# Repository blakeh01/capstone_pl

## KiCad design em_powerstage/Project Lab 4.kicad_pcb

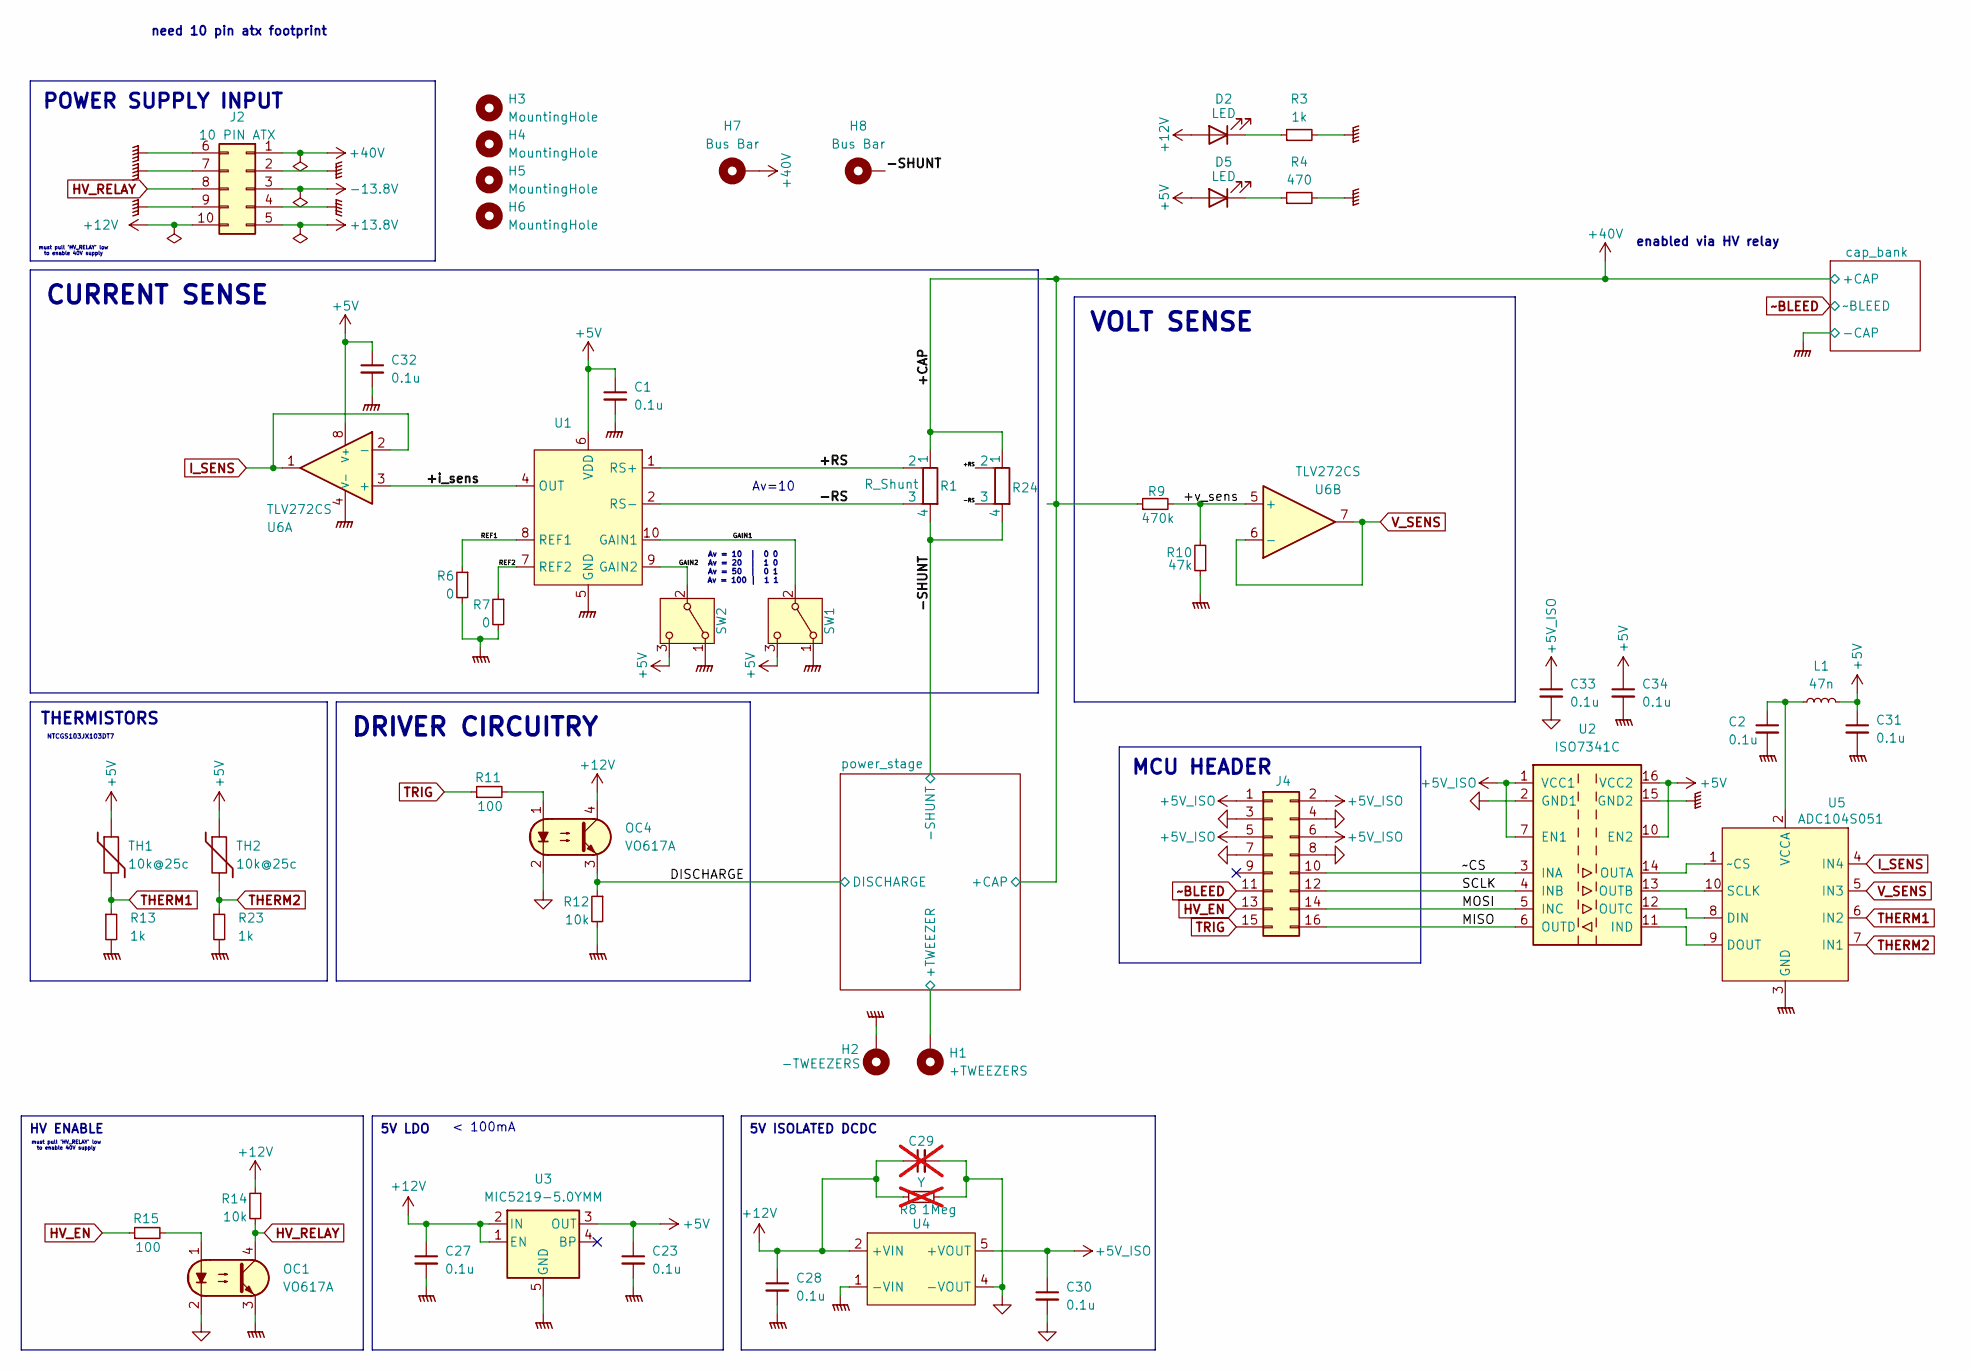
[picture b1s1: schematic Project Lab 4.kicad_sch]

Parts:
C1, C2, C23, C27, C28, C30, C31, C32, C33, C34: 0.1u; C_1206_3216Metric_Pad1.33x1.80mm_HandSolder
C29: Y; C_Disc_D8.0mm_W2.5mm_P5.00mm; not fitted
D2, D5: LED; LED_1206_3216Metric_Pad1.42x1.75mm_HandSolder
H1: +TWEEZERS; MountingHole_4.3mm_M4_Pad
H2: -TWEEZERS; MountingHole_4.3mm_M4_Pad
H3, H4, H5, H6: MountingHole; MountingHole_4mm
H7: Bus Bar; busbar_28mmX155mm
H8: Bus Bar; busbar_35mm_18mm
J2: 10 PIN ATX; Molex_Mini-Fit_Jr_5566-10A_2x05_P4.20mm_Vertical
J4: Conn_02x08_Odd_Even; PinHeader_2x08_P2.54mm_Vertical
L1: 47n; L_1206_3216Metric_Pad1.22x1.90mm_HandSolder
OC1, OC4: VO617A; DIP-4_W7.62mm_LongPads
R1: R_Shunt; CSS4J4026RL500F
R3, R13, R23: 1k; R_0805_2012Metric_Pad1.20x1.40mm_HandSolder
R4: 470; R_0805_2012Metric_Pad1.20x1.40mm_HandSolder
R6, R7: 0; R_0805_2012Metric_Pad1.20x1.40mm_HandSolder
R8: 1Meg; R_Axial_DIN0207_L6.3mm_D2.5mm_P15.24mm_Horizontal; not fitted
R9: 470k; R_0805_2012Metric_Pad1.20x1.40mm_HandSolder
R10: 47k; R_0805_2012Metric_Pad1.20x1.40mm_HandSolder
R11, R15: 100; R_0805_2012Metric_Pad1.20x1.40mm_HandSolder
R12, R14: 10k; R_0805_2012Metric_Pad1.20x1.40mm_HandSolder
R24: R_Shunt; CSM2F6918L050J21
SW1, SW2: SW_SPDT; SW_E-Switch_EG1271_SPDT
TH1, TH2: 10k@25c; R_0402_1005Metric_Pad0.72x0.64mm_HandSolder
U1: TDFN-10-SMD
U2: ISO7341C; SOIC-16W_7.5x10.3mm_P1.27mm
U3: MIC5219-5.0YMM; MSOP-8_3x3mm_P0.65mm
U4: 1769405241
U5: ADC104S051; MSOP-10-1EP_3x3mm_P0.5mm_EP1.73x1.98mm
U6: TLV272CS; SO-8_3.9x4.9mm_P1.27mm

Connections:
+5V: C1.1, C23.1, C31.1, C32.1, C34.1, D5.2 (A), L1.2, SW1.3 (C), SW2.3 (C), TH1.1, TH2.1, U1.6 (VDD), U2.10 (EN2), U2.16 (VCC2), U3.3 (OUT), U6.8 (V+)
+5V_ISO: C30.1, C33.1, J4.1, J4.2, J4.5, J4.6, U2.1 (VCC1), U2.7 (EN1), U4.5 (+VOUT)
+12V: C27.1, C28.1, C29.1, D2.2 (A), J2.10, OC4.4, R8.1, R14.1, U3.1 (EN), U3.2 (IN), U4.2 (+VIN); also elsewhere on the board
+13.8V: J2.5
+40V: H7.1, J2.1, R1.1, R9.1, R24.1; also elsewhere on the board
-13.8V: J2.3
/+RS: R1.2, R24.2, U1.1 (RS+)
/+i_sens: U1.4 (OUT), U6.3 (+)
/+v_sens: R9.2, R10.2, U6.5 (+)
/-RS: R1.3, R24.3, U1.2 (RS-)
/-SHUNT: H8.1, R1.4, R24.4; also elsewhere on the board
/DISCHARGE: OC4.3, R12.1; also elsewhere on the board
/GAIN1: SW1.2 (B), U1.10 (GAIN1)
/GAIN2: SW2.2 (B), U1.9 (GAIN2)
/MISO: J4.16, U2.6 (OUTD)
/MOSI: J4.14, U2.5 (INC)
/REF1: R6.1, U1.8 (REF1)
/REF2: R7.1, U1.7 (REF2)
/SCLK: J4.12, U2.4 (INB)
/power_stage/+TWEEZER: H1.1; also elsewhere on the board
/~CS: J4.10, U2.3 (INA)
GND: C29.2, C30.2, C33.2, J4.3, J4.4, J4.7, J4.8, OC1.2, OC4.2, R8.2, U2.2 (GND1), U2.8 (GND1), U4.4 (-VOUT); also elsewhere on the board
GNDPWR: C1.2, C2.2, C23.2, C27.2, C28.2, C31.2, C32.2, C34.2, H2.1, J2.2, J2.4, J2.6, J2.7, J2.9, OC1.3, R3.2, R4.2, R6.2, R7.2, R10.1, R12.2, R13.2, R23.2, SW1.1 (A), SW2.1 (A), U1.5 (GND), U2.9 (GND2), U2.15 (GND2), U3.5 (GND), U3.6 (GND), U3.7 (GND), U3.8 (GND), U4.1 (-VIN), U5.3 (GND), U6.4 (V-); also elsewhere on the board
HV_EN: J4.13, R15.1
HV_RELAY: J2.8, OC1.4, R14.2
I_SENS: U5.4 (IN4), U6.1, U6.2 (-)
unnamed: D2.1 (K), R3.1
unnamed: D5.1 (K), R4.1
unnamed: OC1.1, R15.2
unnamed: OC4.1, R11.2
unnamed: U2.11 (IND), U5.9 (DOUT)
unnamed: U2.14 (OUTA), U5.1 (~CS)
unnamed: U2.13 (OUTB), U5.10 (SCLK)
unnamed: U2.12 (OUTC), U5.8 (DIN)
unnamed: C2.1, L1.1, U5.2 (VCCA)
THERM1: R13.1, TH1.2, U5.6 (IN2)
THERM2: R23.1, TH2.2, U5.7 (IN1)
TRIG: J4.15, R11.1
V_SENS: U5.5 (IN3), U6.6 (-), U6.7
~BLEED: J4.11; also elsewhere on the board

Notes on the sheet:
POWER SUPPLY INPUT
5V ISOLATED DCDC
MCU HEADER
HV ENABLE
DRIVER CIRCUITRY
5V LDO
CURRENT SENSE
VOLT SENSE
THERMISTORS
must pull 'HV_RELAY' low to enable 40V supply
enabled via HV relay
NTCGS103JX103DT7
need 10 pin atx footprint
< 100mA
Av = 10 | 0 0 Av = 20 | 1 0 Av = 50 | 0 1 Av = 100 | 1 1
Av=10

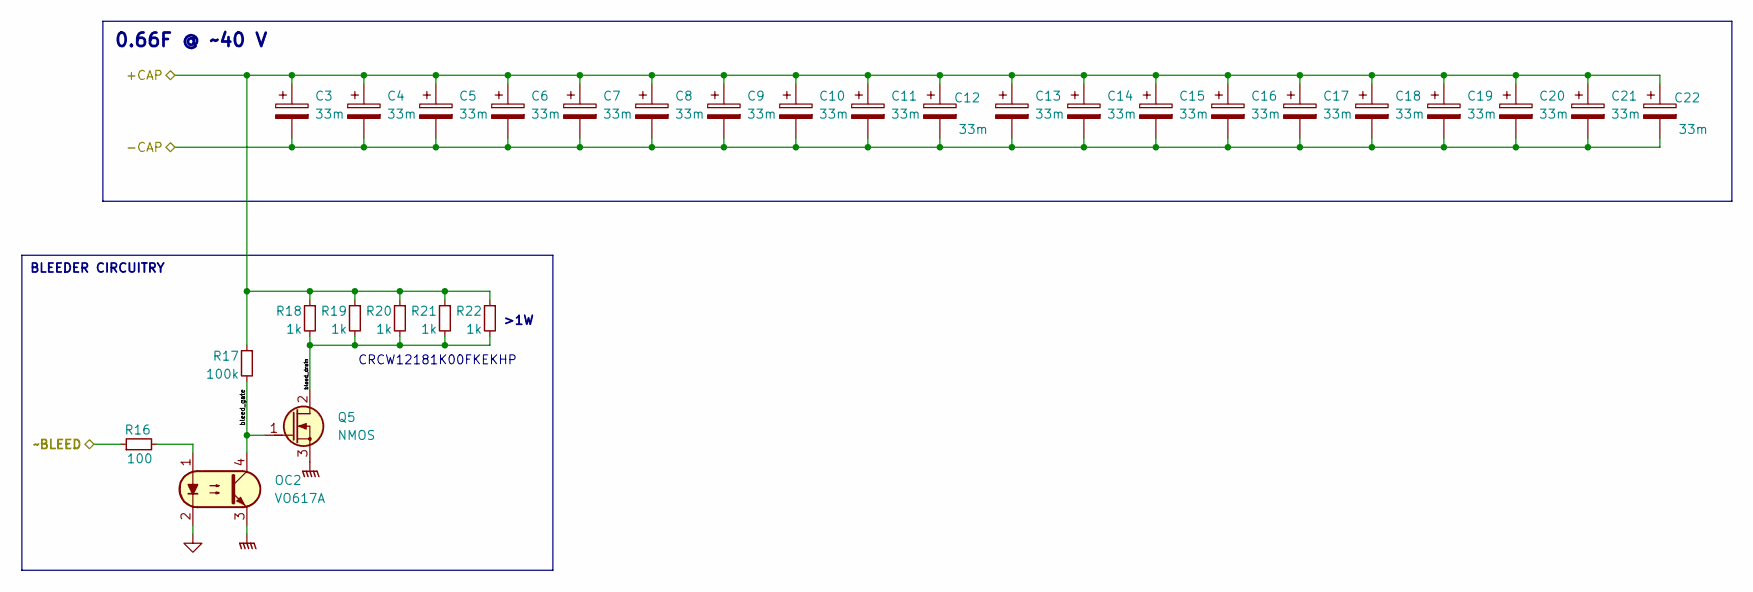
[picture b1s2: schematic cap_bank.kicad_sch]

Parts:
C3, C4, C5, C6, C7, C8, C9, C10, C11, C12, C13, C14, C15, C16, C17, C18, C19, C20, C21, C22: 33m; CAPPRD1000W190D3550H8200
OC2: VO617A; DIP-4_W7.62mm_LongPads
Q5: NMOS; SOT-23-3
R16: 100; R_0805_2012Metric_Pad1.20x1.40mm_HandSolder
R17: 100k; R_0805_2012Metric_Pad1.20x1.40mm_HandSolder
R18, R19, R20, R21, R22: 1k; R_1218_3246Metric_Pad1.22x4.75mm_HandSolder

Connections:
+40V: C3.1, C4.1, C5.1, C6.1, C7.1, C8.1, C9.1, C10.1, C11.1, C12.1, C13.1, C14.1, C15.1, C16.1, C17.1, C18.1, C19.1, C20.1, C21.1, C22.1, R17.1, R18.1, R19.1, R20.1, R21.1, R22.1; also elsewhere on the board
/cap_bank/bleed_drain: Q5.2 (D), R18.2, R19.2, R20.2, R21.2, R22.2
/cap_bank/bleed_gate: OC2.4, Q5.1 (G), R17.2
GND: OC2.2; also elsewhere on the board
GNDPWR: C3.2, C4.2, C5.2, C6.2, C7.2, C8.2, C9.2, C10.2, C11.2, C12.2, C13.2, C14.2, C15.2, C16.2, C17.2, C18.2, C19.2, C20.2, C21.2, C22.2, OC2.3, Q5.3 (S); also elsewhere on the board
unnamed: OC2.1, R16.2
~BLEED: R16.1; also elsewhere on the board

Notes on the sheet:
BLEEDER CIRCUITRY
0.66F @ ~40 V
CRCW12181K00FKEKHP
>1W

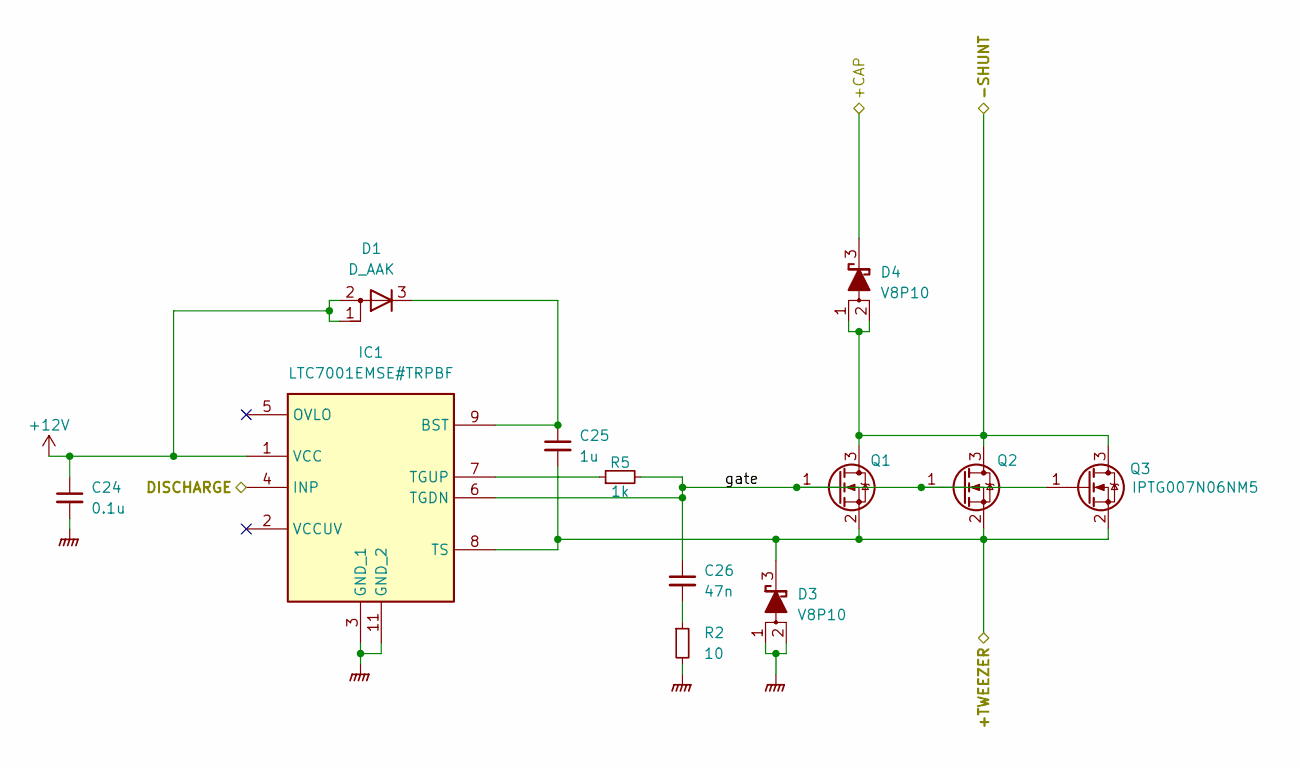
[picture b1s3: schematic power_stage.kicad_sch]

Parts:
C24: 0.1u; C_1206_3216Metric_Pad1.33x1.80mm_HandSolder
C25: 1u; C_1206_3216Metric_Pad1.33x1.80mm_HandSolder
C26: 47n; C_0805_2012Metric_Pad1.18x1.45mm_HandSolder
D1: D_AAK; SOT-23-3
D3, D4: V8P10; TO-277A
IC1: LTC7001EMSE#TRPBF; SOP50P490X110-11N; Mouser Part Number 584-7001EMSETRPBF
Q1, Q2, Q3: IPTG007N06NM5; HSOG_8-3
R2: 10; R_0805_2012Metric_Pad1.20x1.40mm_HandSolder
R5: 1k; R_0805_2012Metric_Pad1.20x1.40mm_HandSolder

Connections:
+12V: C24.1, D1.1 (A), D1.2 (A), IC1.1 (VCC); also elsewhere on the board
+40V: D4.3 (K); also elsewhere on the board
/-SHUNT: D4.1 (A), D4.2 (A), Q1.3 (D), Q2.3 (D), Q3.3 (D); also elsewhere on the board
/DISCHARGE: IC1.4 (INP); also elsewhere on the board
/power_stage/+TWEEZER: C25.2, D3.3 (K), IC1.8 (TS), Q1.2 (S), Q2.2 (S), Q3.2 (S); also elsewhere on the board
/power_stage/gate: C26.1, IC1.6 (TGDN), Q1.1 (G), Q2.1 (G), Q3.1 (G), R5.2
GNDPWR: C24.2, D3.1 (A), D3.2 (A), IC1.3 (GND_1), IC1.11 (GND_2), R2.2; also elsewhere on the board
unnamed: C26.2, R2.1
unnamed: C25.1, D1.3 (K), IC1.9 (BST)
unnamed: IC1.7 (TGUP), R5.1

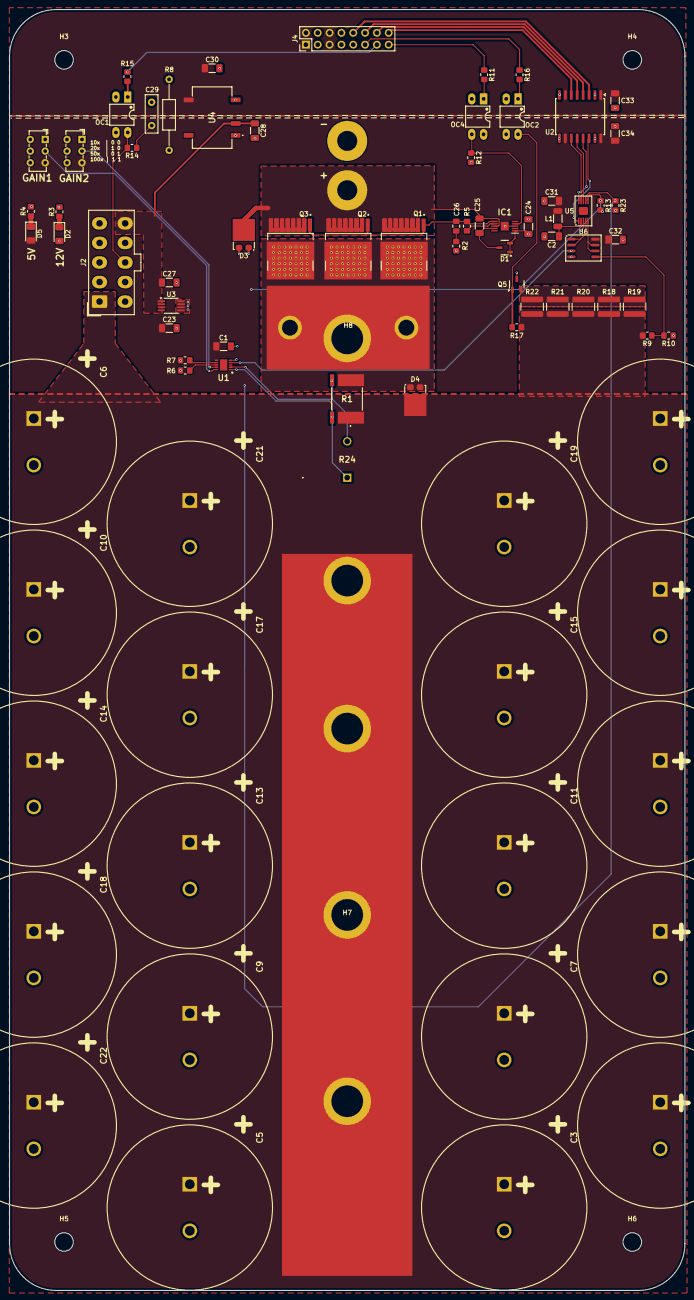
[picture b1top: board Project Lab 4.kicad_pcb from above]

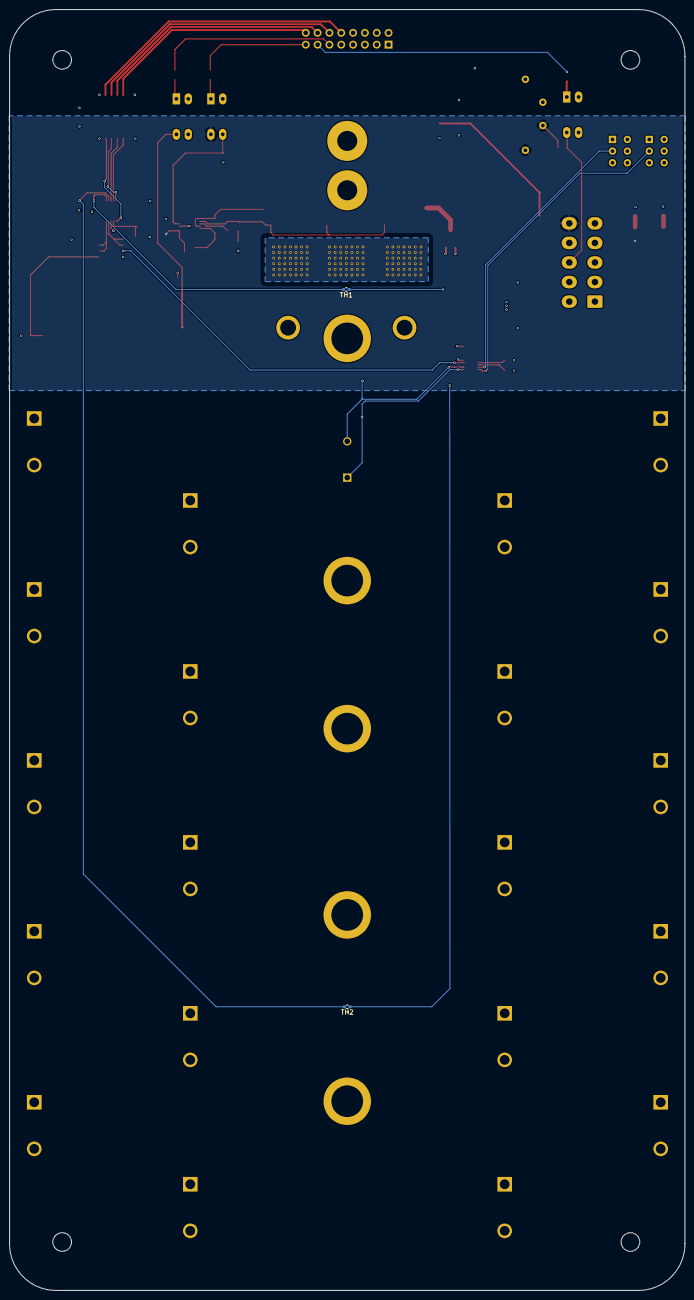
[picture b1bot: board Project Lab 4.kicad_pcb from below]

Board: 4 copper layers, 145.0 x 275.0 mm, 92 parts (2 on the bottom side), 45 nets.

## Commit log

2024-09-30 updated power stage board
